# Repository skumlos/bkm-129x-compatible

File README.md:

Completely untested BKM-129X compatible board made in Kicad.

There are still some components to be decided.

Should be used together with an Arduino Nano v3 with the code loaded from https://github.com/skumlos/bkm-129x-mcu

More here: https://immerhax.com/?p=422

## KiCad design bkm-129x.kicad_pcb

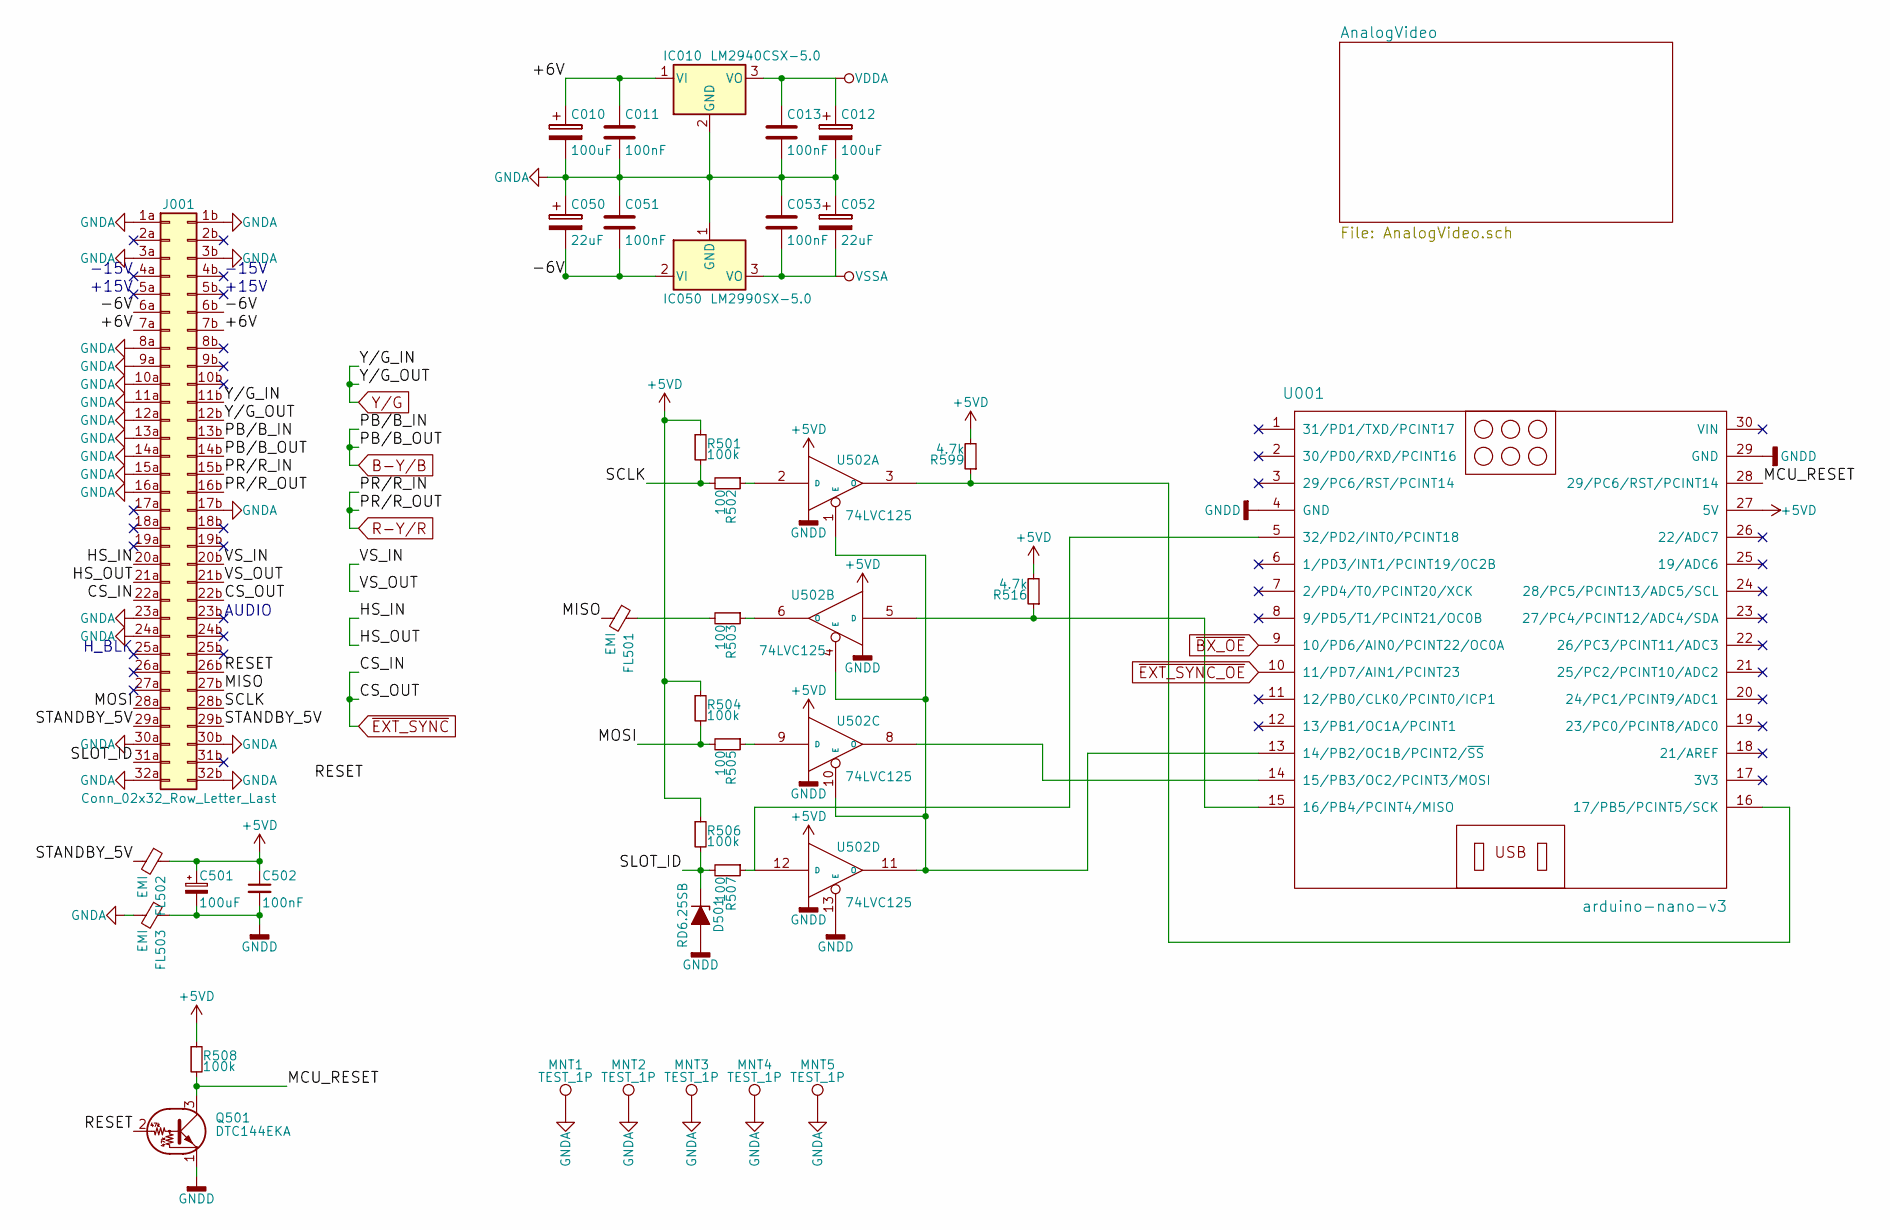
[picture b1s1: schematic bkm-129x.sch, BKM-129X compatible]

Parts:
C010, C012, C501: 100uF; CP_Elec_6.3x5.3
C011, C013, C051, C053, C502: 100nF; C_0805_HandSoldering
C050, C052: 22uF; CP_Elec_6.3x5.3
D501: RD6.25SB; D_SOD-123
FL501, FL502, FL503: EMI; R_0805_HandSoldering
IC010: LM2940CSX-5.0; SOT-223-3Lead_TabPin2
IC050: LM2990SX-5.0; TO-263-3_TabPin2
J001: Conn_02x32_Row_Letter_Last; DIN-41612-64P
MNT1, MNT2, MNT3, MNT4, MNT5: TEST_1P; MountingHole_2.7mm_M2.5_DIN965_Pad
Q501: DTC144EKA; SOT-23_Handsoldering
R501, R504, R506, R508: 100k; R_0805_HandSoldering
R502, R503, R505, R507: 100; R_0805_HandSoldering
R516, R599: 4.7k; R_0805_HandSoldering
U001: arduino-nano-v3
U502: 74LVC125; SOIC-14_3.9x8.7mm_Pitch1.27mm

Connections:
+5VD: C501.1, C502.1, FL502.1, R501.1, R504.1, R506.1, R508.1, R516.2, R599.2, U001.27 (5V), U502.14 (VCC)
/+6V: C010.1, C011.1, IC010.1 (VI), J001.7a, J001.7b
/-6V: C050.2, C051.2, IC050.2 (VI), J001.6a, J001.6b
/HS_IN: J001.20a, J001.21a
/MCU_RESET: Q501.3 (C), R508.2, U001.28 (29/PC6/RST/PCINT14)
/MISO: FL501.2, J001.27b
/MOSI: J001.28a, R504.2, R505.2
/RESET: J001.26b, Q501.2 (B)
/SCLK: J001.28b, R501.2, R502.2
/SLOT_ID: D501.1 (K), J001.31a, R506.2, R507.2
/STANDBY_5V: FL502.2, J001.29a, J001.29b
/VS_IN: J001.20b, J001.21b
B-Y/B: J001.13b, J001.14b; also elsewhere on the board
GND: C501.2, C502.2, D501.2 (A), FL503.1, Q501.1 (E), U001.4 (GND), U001.29 (GND), U502.7 (GND), U502.13 (E)
GNDA: C010.2, C011.2, C012.2, C013.2, C050.1, C051.1, C052.1, C053.1, FL503.2, IC010.2 (GND), IC050.1 (GND), J001.1a, J001.1b, J001.3a, J001.3b, J001.8a, J001.9a, J001.10a, J001.11a, J001.12a, J001.13a, J001.14a, J001.15a, J001.16a, J001.17b, J001.23a, J001.24a, J001.30a, J001.30b, J001.32a, J001.32b, MNT1.1, MNT2.1, MNT3.1, MNT4.1, MNT5.1; also elsewhere on the board
unnamed: FL501.1, R503.2
unnamed: R502.1, U502.2 (D)
unnamed: R503.1, U502.6 (O)
unnamed: R505.1, U502.9 (D)
unnamed: R507.1, U001.5 (32/PD2/INT0/PCINT18), U502.12 (D)
unnamed: R516.1, U001.15 (16/PB4/PCINT4/MISO), U502.5 (D)
unnamed: R599.1, U001.16 (17/PB5/PCINT5/SCK), U502.3 (O)
unnamed: U001.13 (14/PB2/OC1B/PCINT2/~SS), U502.1 (E), U502.4 (E), U502.10 (E), U502.11 (O)
unnamed: U001.14 (15/PB3/OC2/PCINT3/MOSI), U502.8 (O)
R-Y/R: J001.15b, J001.16b; also elsewhere on the board
VDDA: C012.1, C013.1, IC010.3 (VO); also elsewhere on the board
VSSA: C052.2, C053.2, IC050.3 (VO); also elsewhere on the board
Y/G: J001.11b, J001.12b; also elsewhere on the board
~BX_OE: U001.9 (10/PD6/AIN0/PCINT22/OC0A); also elsewhere on the board
~EXT_SYNC: J001.22a, J001.22b; also elsewhere on the board
~EXT_SYNC_OE: U001.10 (11/PD7/AIN1/PCINT23); also elsewhere on the board

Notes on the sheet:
-15V
+15V
AUDIO
H_BLK

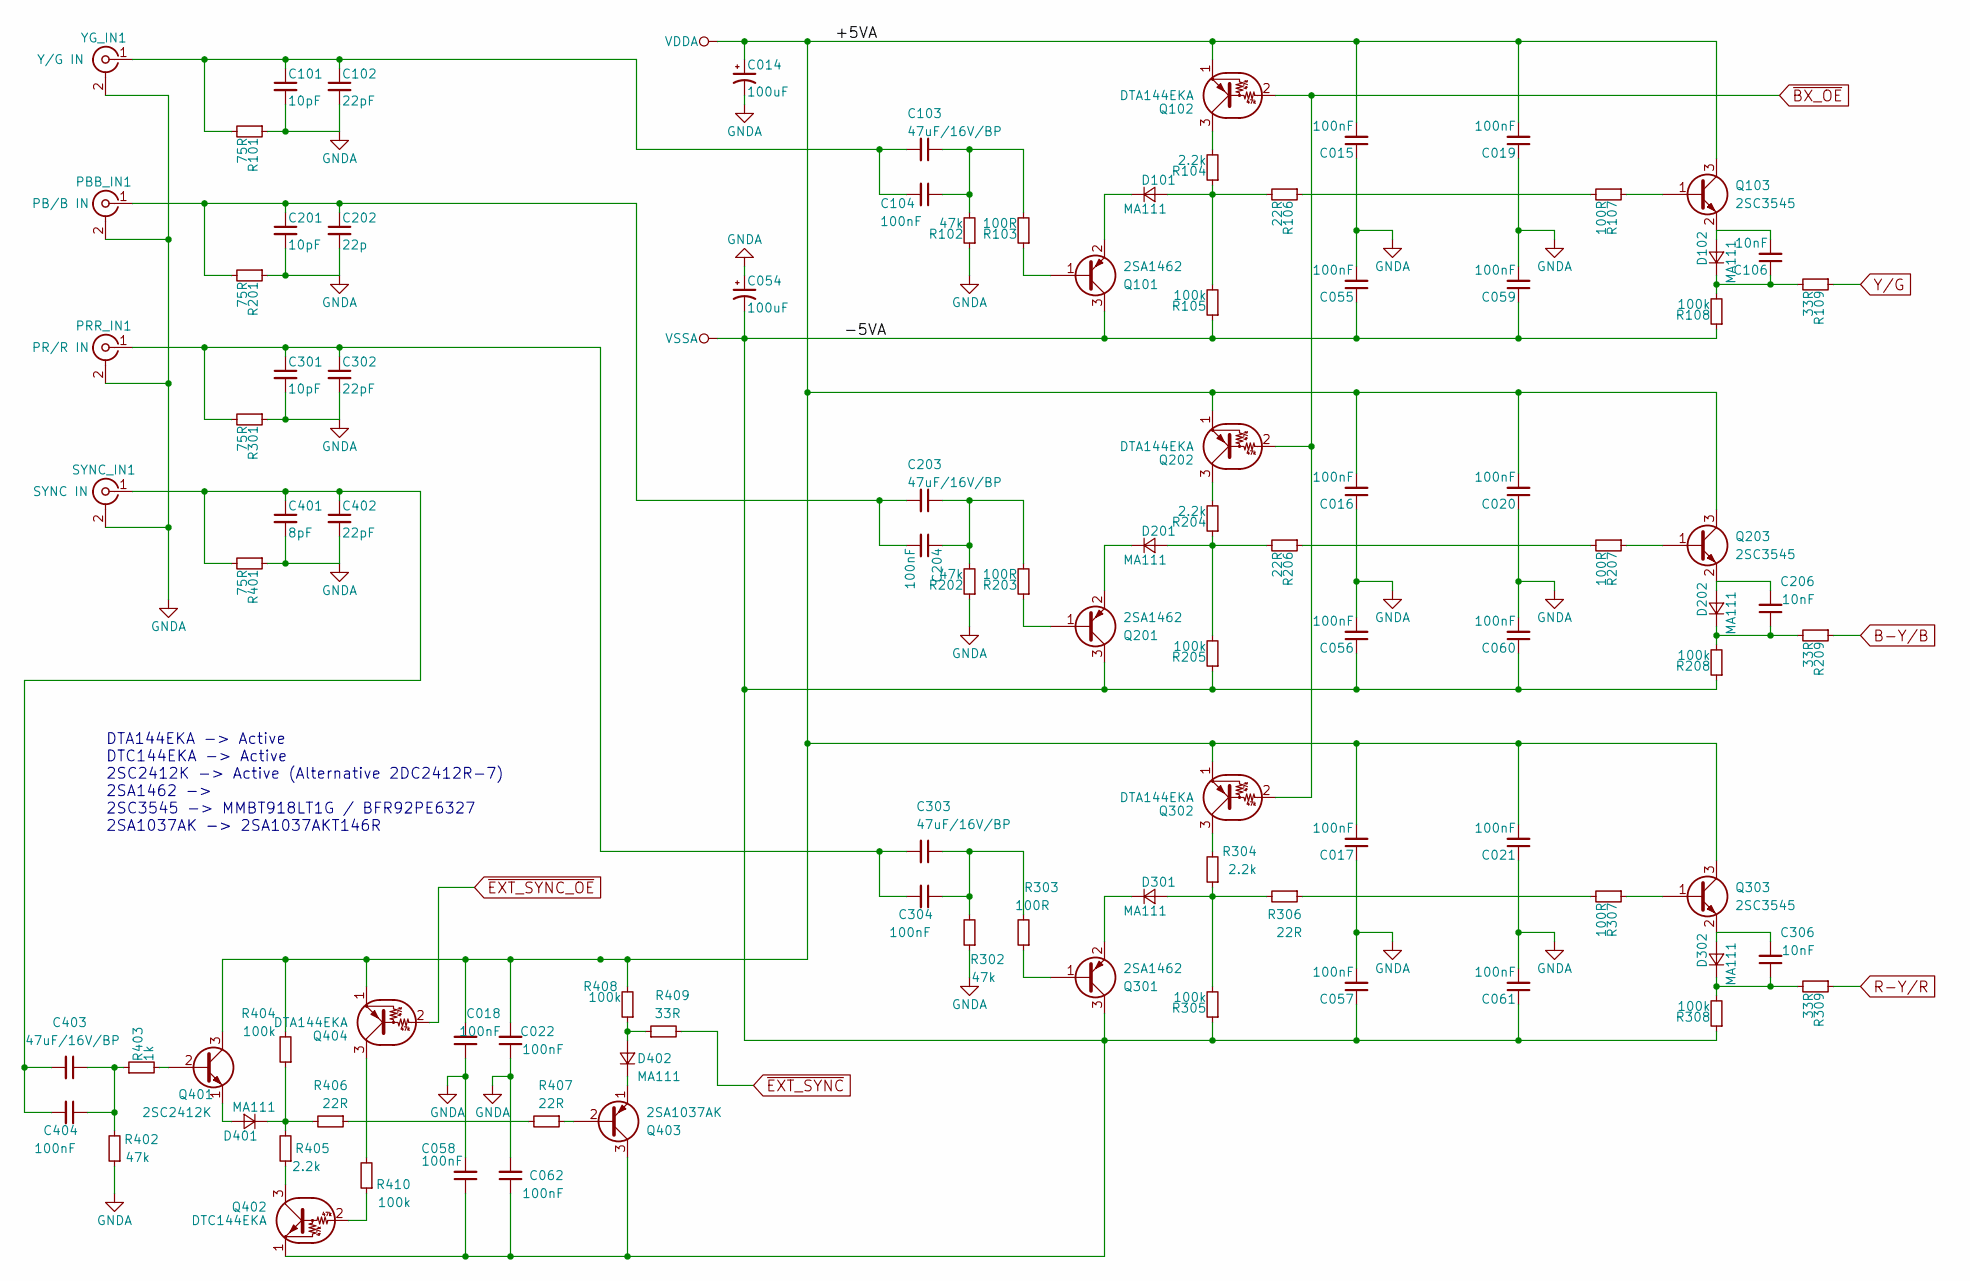
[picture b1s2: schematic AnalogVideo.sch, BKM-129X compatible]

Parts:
C014, C054: 100uF; CP_Elec_6.3x5.3
C015, C016, C017, C018, C019, C020, C021, C022, C055, C056, C057, C058, C059, C060, C061, C062, C104, C204, C304, C404: 100nF; C_0805_HandSoldering
C101, C201, C301: 10pF; C_0805_HandSoldering
C102, C302, C402: 22pF; C_0805_HandSoldering
C103, C203, C303, C403: 47uF/16V/BP; CP_Elec_8x5.4
C106, C206, C306: 10nF; C_0805_HandSoldering
C202: 22p; C_0805_HandSoldering
C401: 8pF; C_0805_HandSoldering
D101, D102, D201, D202, D301, D302, D401, D402: MA111; D_SOD-123
PBB_IN1: PB/B IN; BNC-THT
PRR_IN1: PR/R IN; BNC-THT
Q101, Q201, Q301: 2SA1462; SOT-23_Handsoldering
Q102, Q202, Q302, Q404: DTA144EKA; SOT-23_Handsoldering
Q103, Q203, Q303: 2SC3545; SOT-23_Handsoldering
Q401: 2SC2412K; SOT-23_Handsoldering
Q402: DTC144EKA; SOT-23_Handsoldering
Q403: 2SA1037AK; SOT-23_Handsoldering
R101, R201, R301, R401: 75R; R_0805_HandSoldering
R102, R202, R302, R402: 47k; R_0805_HandSoldering
R103, R107, R203, R207, R303, R307: 100R; R_0805_HandSoldering
R104, R204, R304, R405: 2.2k; R_0805_HandSoldering
R105, R108, R205, R208, R305, R308, R404, R408, R410: 100k; R_0805_HandSoldering
R106, R206, R306, R406, R407: 22R; R_0805_HandSoldering
R109, R209, R309, R409: 33R; R_0805_HandSoldering
R403: 1k; R_0805_HandSoldering
SYNC_IN1: SYNC IN; BNC-THT
YG_IN1: Y/G IN; BNC-THT

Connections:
B-Y/B: R209.1; also elsewhere on the board
GNDA: C014.2, C015.1, C016.1, C017.1, C018.1, C019.1, C020.1, C021.1, C022.1, C054.1, C055.2, C056.2, C057.2, C058.2, C059.2, C060.2, C061.2, C062.2, C101.2, C102.2, C201.2, C202.2, C301.2, C302.2, C401.2, C402.2, PBB_IN1.2 (Ext), PRR_IN1.2 (Ext), R101.1, R102.1, R201.1, R202.1, R301.1, R302.1, R401.1, R402.1, SYNC_IN1.2 (Ext), YG_IN1.2 (Ext); also elsewhere on the board
unnamed: C101.1, C102.1, C103.2, C104.2, R101.2, YG_IN1.1 (In)
unnamed: C103.1, C104.1, R102.2, R103.2
unnamed: C106.1, D102.1 (K), R108.2, R109.2
unnamed: C106.2, D102.2 (A), Q103.2 (E)
unnamed: C201.1, C202.1, C203.2, C204.2, PBB_IN1.1 (In), R201.2
unnamed: C203.1, C204.1, R202.2, R203.2
unnamed: C206.1, D202.1 (K), R208.2, R209.2
unnamed: C206.2, D202.2 (A), Q203.2 (E)
unnamed: C301.1, C302.1, C303.2, C304.2, PRR_IN1.1 (In), R301.2
unnamed: C303.1, C304.1, R302.2, R303.2
unnamed: C306.1, D302.1 (K), R308.2, R309.2
unnamed: C306.2, D302.2 (A), Q303.2 (E)
unnamed: C401.1, C402.1, C403.2, C404.2, R401.2, SYNC_IN1.1 (In)
unnamed: C403.1, C404.1, R402.2, R403.1
unnamed: D101.1 (K), Q101.2 (E)
unnamed: D101.2 (A), R104.1, R105.2, R106.2
unnamed: D201.1 (K), Q201.2 (E)
unnamed: D201.2 (A), R204.1, R205.2, R206.2
unnamed: D301.1 (K), Q301.2 (E)
unnamed: D301.2 (A), R304.1, R305.2, R306.2
unnamed: D401.1 (K), R404.1, R405.2, R406.2
unnamed: D401.2 (A), Q401.1 (E)
unnamed: D402.1 (K), Q403.1 (E)
unnamed: D402.2 (A), R408.1, R409.1
unnamed: Q101.1 (B), R103.1
unnamed: Q102.3 (C), R104.2
unnamed: Q103.1 (B), R107.1
unnamed: Q201.1 (B), R203.1
unnamed: Q202.3 (C), R204.2
unnamed: Q203.1 (B), R207.1
unnamed: Q301.1 (B), R303.1
unnamed: Q302.3 (C), R304.2
unnamed: Q303.1 (B), R307.1
unnamed: Q401.2 (B), R403.2
unnamed: Q402.2 (B), R410.1
unnamed: Q402.3 (C), R405.1
unnamed: Q403.2 (B), R407.1
unnamed: Q404.3 (C), R410.2
unnamed: R106.1, R107.2
unnamed: R206.1, R207.2
unnamed: R306.1, R307.2
unnamed: R406.1, R407.2
R-Y/R: R309.1; also elsewhere on the board
VDDA: C014.1, C015.2, C016.2, C017.2, C018.2, C019.2, C020.2, C021.2, C022.2, Q102.1 (E), Q103.3 (C), Q202.1 (E), Q203.3 (C), Q302.1 (E), Q303.3 (C), Q401.3 (C), Q404.1 (E), R404.2, R408.2; also elsewhere on the board
VSSA: C054.2, C055.1, C056.1, C057.1, C058.1, C059.1, C060.1, C061.1, C062.1, Q101.3 (C), Q201.3 (C), Q301.3 (C), Q402.1 (E), Q403.3 (C), R105.1, R108.1, R205.1, R208.1, R305.1, R308.1; also elsewhere on the board
Y/G: R109.1; also elsewhere on the board
~BX_OE: Q102.2 (B), Q202.2 (B), Q302.2 (B); also elsewhere on the board
~EXT_SYNC: R409.2; also elsewhere on the board
~EXT_SYNC_OE: Q404.2 (B); also elsewhere on the board

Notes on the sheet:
DTA144EKA -> Active DTC144EKA -> Active 2SC2412K -> Active (Alternative 2DC2412R-7) 2SA1462 -> 2SC3545 -> MMBT918LT1G / BFR92PE6327 2SA1037AK -> 2SA1037AKT146R

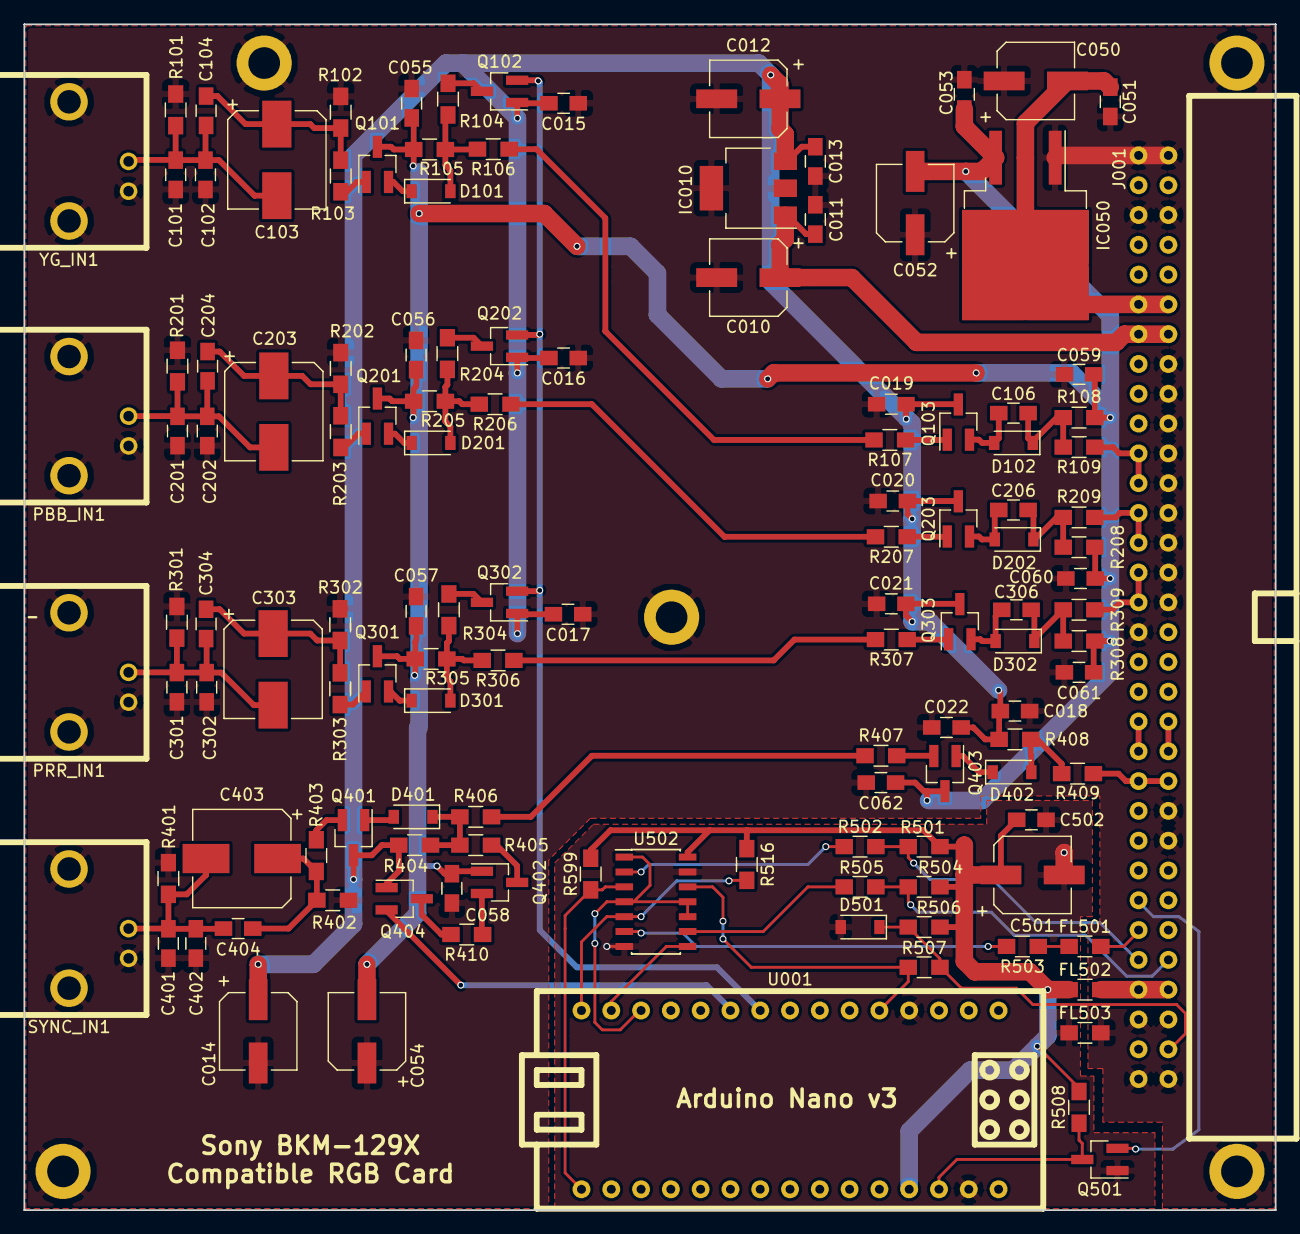
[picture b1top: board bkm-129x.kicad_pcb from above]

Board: 2 copper layers, 106.7 x 101.1 mm, 134 parts (0 on the bottom side), 73 nets.

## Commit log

2020-01-25 Initial untested version
2020-01-26 Minor adjustments
2020-01-27 Switched to 8mm caps for video which should fit SMD bipolar ecaps
2020-01-27 Added readme
2020-01-31 Fixed some footprints
2020-02-18 Added missing pullup resistor on SCLK
